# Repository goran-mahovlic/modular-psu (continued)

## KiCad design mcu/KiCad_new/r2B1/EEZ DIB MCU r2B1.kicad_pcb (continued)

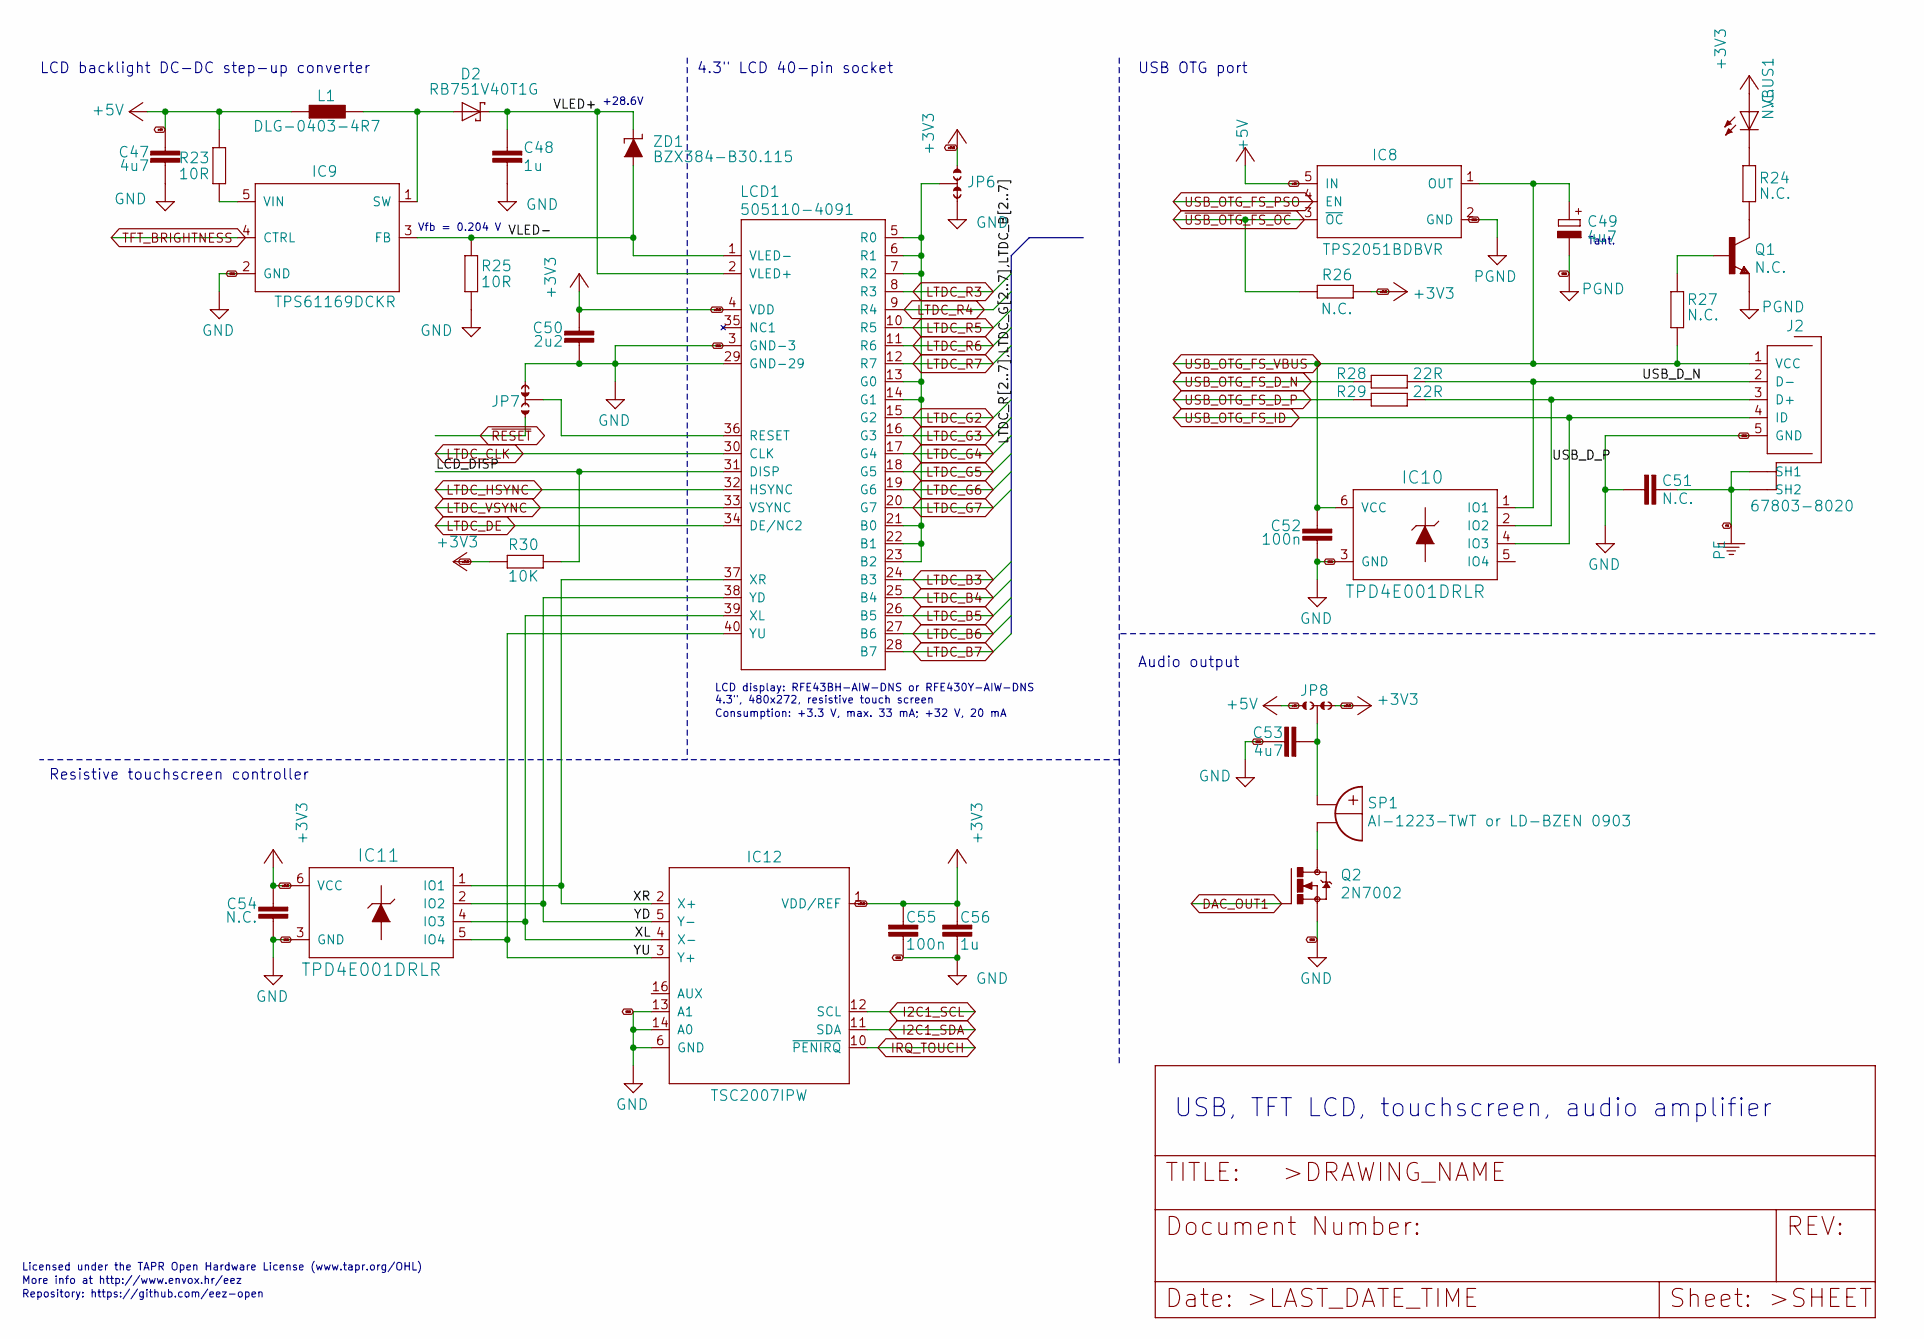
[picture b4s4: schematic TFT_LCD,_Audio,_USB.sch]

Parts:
C47, C53: 4u7; C1206
C48, C56: 1u; C0805
C49: 4u7; EC1206
C50: 2u2; C0805
C51: N.C.; C0805
C52, C55: 100n; C0603
C54: N.C.; C0603
D2: RB751V40T1G; SOD323-R
IC8: TPS2051BDBVR; DBV5
IC9: TPS61169DCKR; DCK5
IC10, IC11: TPD4E001DRLR; DRL6
IC12: TSC2007IPW; PW(R-PDSO-G16)
J2: 67803-8020; 678038020
JP6, JP7, JP8: JP3-CUT
L1: DLG-0403-4R7; DE0403
LCD1: 505110-4091; FPC_40
Q1: N.C.; SOT23-BEC
Q2: 2N7002; SOT103P240X110-3N
R23, R25: 10R; R0805
R24, R26, R27: N.C.; R0805
R28, R29: 22R; R0805
R30: 10K; R0805
SP1: AI-1223-TWT or LD-BZEN 0903; AI-1223-TWT_COMBO
VBUS: N.C.; LED_0805
ZD1: BZX384-B30.115; SOD323-W

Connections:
+3V3: C50.1, C54.2, C55.2, C56.2, IC11.6 (VCC), IC12.1 (VDD/REF), JP6.NO, JP8.NC, LCD1.4 (VDD), R26.2, R30.2; also elsewhere on the board
+5V: C47.1, IC8.5 (IN), JP8.NO, L1.1, R23.1; also elsewhere on the board
/TFT LCD, Audio, USB/LCD_DISP: LCD1.31 (DISP), R30.1
/TFT LCD, Audio, USB/USB_D_N: IC10.1 (IO1), J2.2 (D-), R28.1
/TFT LCD, Audio, USB/USB_D_P: IC10.2 (IO2), J2.3 (D+), R29.1
/TFT LCD, Audio, USB/VLED+: C48.1, D2.C, LCD1.2 (VLED+), ZD1.C
/TFT LCD, Audio, USB/VLED-: IC9.3 (FB), LCD1.1 (VLED-), R25.1, ZD1.A
/TFT LCD, Audio, USB/XL: IC11.4 (IO3), IC12.4 (X-), LCD1.39 (XL)
/TFT LCD, Audio, USB/XR: IC11.1 (IO1), IC12.2 (X+), LCD1.37 (XR)
/TFT LCD, Audio, USB/YD: IC11.2 (IO2), IC12.5 (Y-), LCD1.38 (YD)
/TFT LCD, Audio, USB/YU: IC11.5 (IO4), IC12.3 (Y+), LCD1.40 (YU)
DAC_OUT1: Q2.1 (G); also elsewhere on the board
GND: C47.2, C48.2, C49.-, C50.2, C51.2, C52.1, C53.1, C54.1, C55.1, C56.1, IC8.2 (GND), IC9.2 (GND), IC10.3 (GND), IC11.3 (GND), IC12.6 (GND), IC12.13 (A1), IC12.14 (A0), J2.5 (GND), JP6.NC, JP7.NC, LCD1.3 (GND-3), LCD1.29 (GND-29), Q1.E, Q2.2 (S), R25.2; also elsewhere on the board
I2C1_SCL: IC12.12 (SCL); also elsewhere on the board
I2C1_SDA: IC12.11 (SDA); also elsewhere on the board
IRQ_TOUCH: IC12.10 (~PENIRQ); also elsewhere on the board
LTDC_B3: LCD1.24 (B3); also elsewhere on the board
LTDC_B4: LCD1.25 (B4); also elsewhere on the board
LTDC_B5: LCD1.26 (B5); also elsewhere on the board
LTDC_B6: LCD1.27 (B6); also elsewhere on the board
LTDC_B7: LCD1.28 (B7); also elsewhere on the board
LTDC_CLK: LCD1.30 (CLK); also elsewhere on the board
LTDC_DE: LCD1.34 (DE/NC2); also elsewhere on the board
LTDC_G2: LCD1.15 (G2); also elsewhere on the board
LTDC_G3: LCD1.16 (G3); also elsewhere on the board
LTDC_G4: LCD1.17 (G4); also elsewhere on the board
LTDC_G5: LCD1.18 (G5); also elsewhere on the board
LTDC_G6: LCD1.19 (G6); also elsewhere on the board
LTDC_G7: LCD1.20 (G7); also elsewhere on the board
LTDC_HSYNC: LCD1.32 (HSYNC); also elsewhere on the board
LTDC_R3: LCD1.8 (R3); also elsewhere on the board
LTDC_R4: LCD1.9 (R4); also elsewhere on the board
LTDC_R5: LCD1.10 (R5); also elsewhere on the board
LTDC_R6: LCD1.11 (R6); also elsewhere on the board
LTDC_R7: LCD1.12 (R7); also elsewhere on the board
LTDC_VSYNC: LCD1.33 (VSYNC); also elsewhere on the board
unnamed: C53.2, JP8.COM, SP1.+B (+), SP1.+B.1 (+)
unnamed: D2.A, IC9.1 (SW), L1.2
unnamed: IC9.5 (VIN), R23.2
unnamed: JP6.COM, LCD1.5 (R0), LCD1.6 (R1), LCD1.7 (R2), LCD1.13 (G0), LCD1.14 (G1), LCD1.21 (B0), LCD1.22 (B1), LCD1.23 (B2)
unnamed: JP7.COM, LCD1.36 (RESET)
unnamed: Q1.B, R27.2
unnamed: Q1.C, R24.1
unnamed: Q2.3 (D), SP1.-B (-), SP1.-B.1 (-)
unnamed 195: R24.2; also elsewhere on the board
PE: C51.1, J2.SH1, J2.SH1.1 (SH1), J2.SH2, J2.SH2.2 (SH2); also elsewhere on the board
TFT_BRIGHTNESS: IC9.4 (CTRL); also elsewhere on the board
USB_OTG_FS_D_N: R28.2; also elsewhere on the board
USB_OTG_FS_D_P: R29.2; also elsewhere on the board
USB_OTG_FS_ID: IC10.4 (IO3), J2.4 (ID); also elsewhere on the board
USB_OTG_FS_PSO: IC8.4 (EN); also elsewhere on the board
USB_OTG_FS_VBUS: C49.+, C52.2, IC8.1 (OUT), IC10.6 (VCC), J2.1 (VCC), R27.1; also elsewhere on the board
~RESET: JP7.NO; also elsewhere on the board
~USB_OTG_FS_OC: IC8.3 (~OC), R26.1; also elsewhere on the board

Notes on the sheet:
USB, TFT LCD, touchscreen, audio amplifier
Licensed under the TAPR Open Hardware License (www.tapr.org/OHL)
Repository: https://github.com/eez-open
More info at http://www.envox.hr/eez
4.3" LCD 40-pin socket
LCD backlight DC-DC step-up converter
Consumption: +3.3 V, max. 33 mA; +32 V, 20 mA
Vfb = 0.204 V
LCD display: RFE43BH-AIW-DNS or RFE430Y-AIW-DNS 4.3", 480x272, resistive touch screen
USB OTG port
Resistive touchscreen controller
Audio output
Tant.
+28.6V

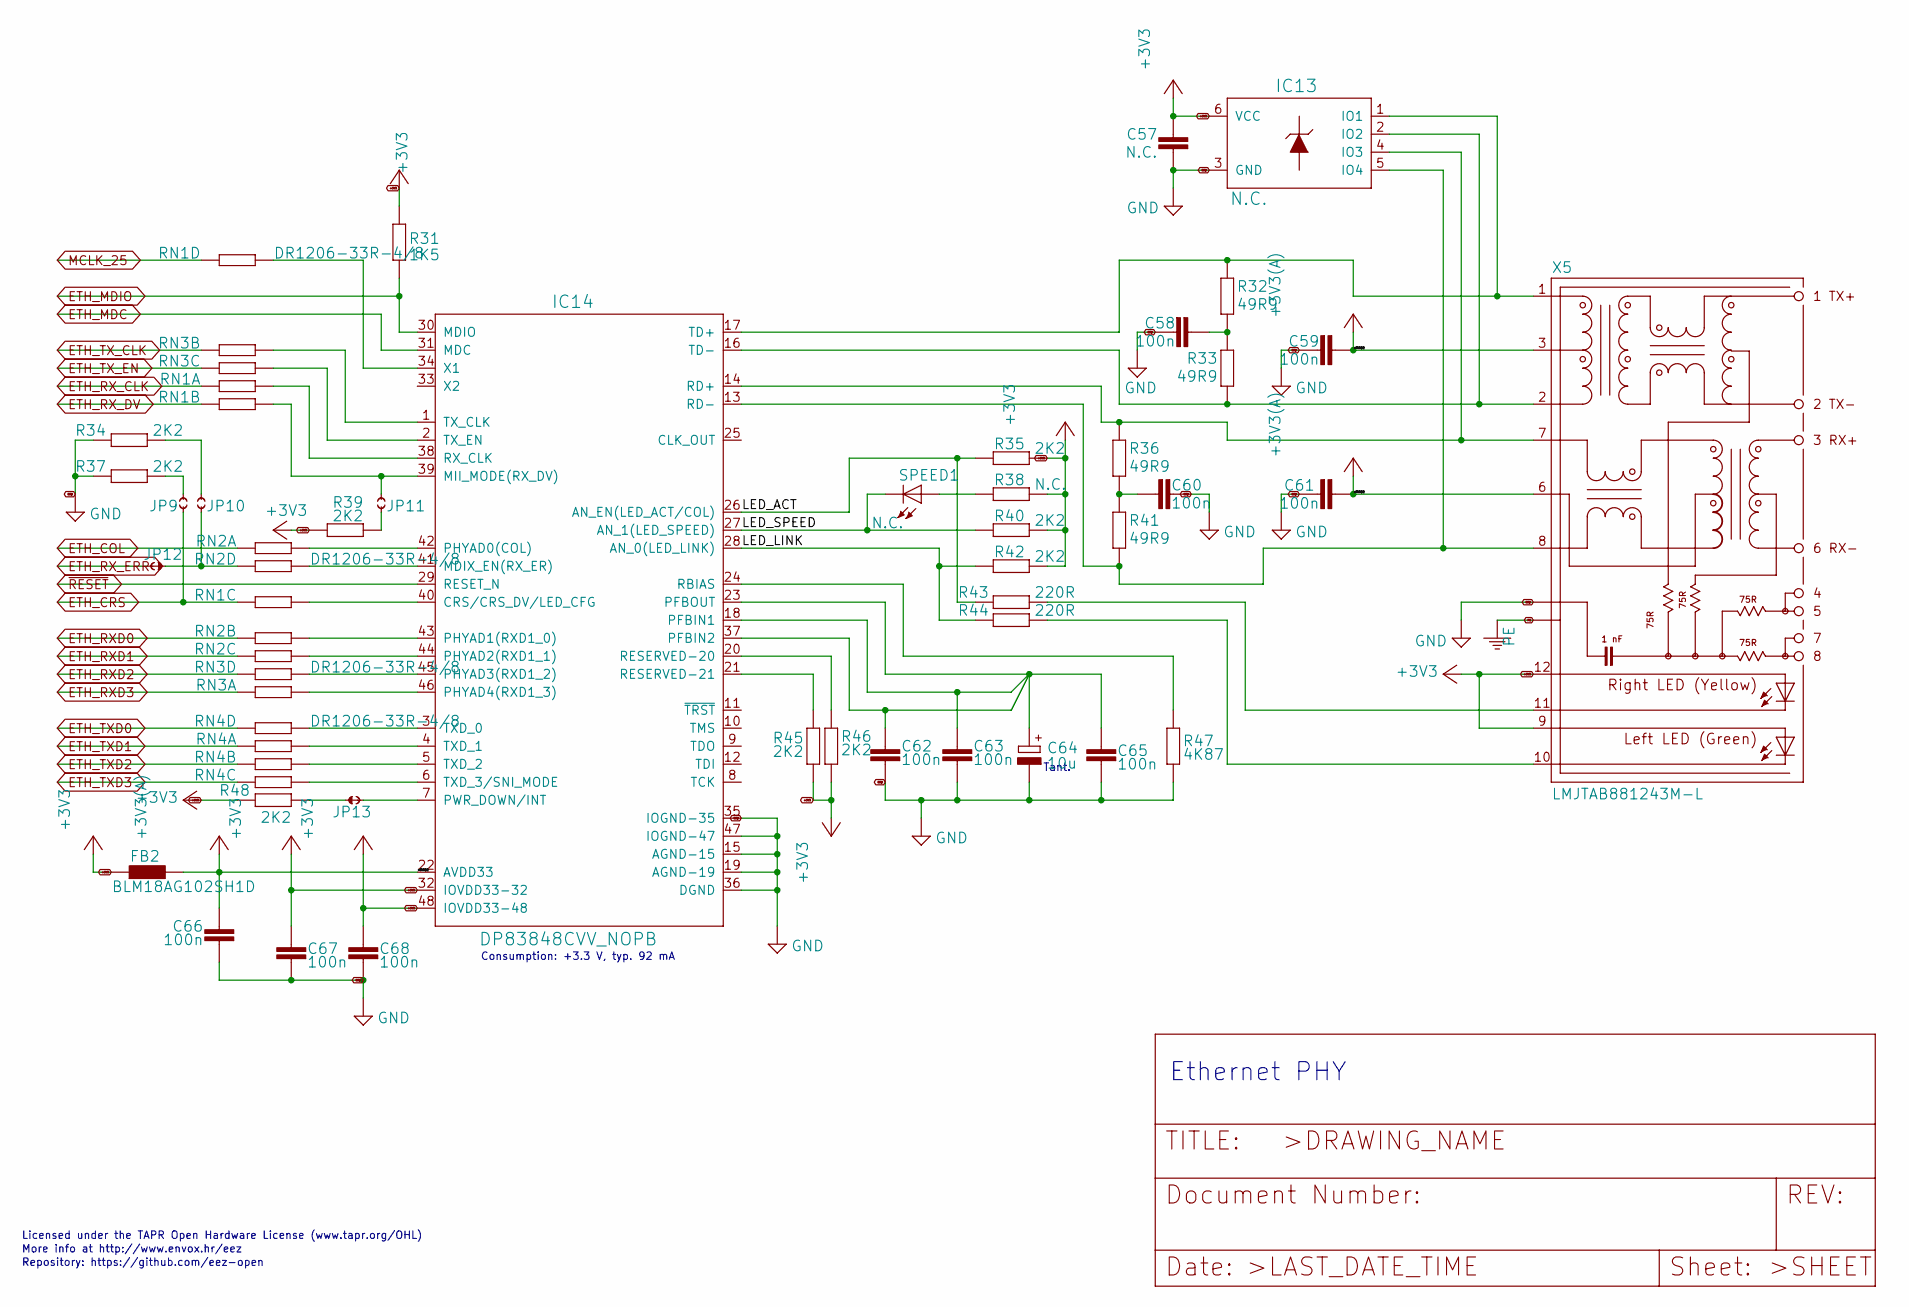
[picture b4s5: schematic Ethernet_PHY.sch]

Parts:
C57: N.C.; C0603
C58, C59, C60, C61, C62, C63, C65, C66, C67, C68: 100n; C0603
C64: 10u; EC1206
FB2: BLM18AG102SH1D; BEAD0603
IC13: N.C.; DRL6
IC14: DP83848CVV_NOPB; PT48
JP9, JP10, JP11: JP2-CUT
JP12, JP13: JP2-NOCUT
R31: 1K5; R0805
R32, R33, R36, R41: 49R9; R0805
R34, R35, R37, R39, R40, R42, R45, R46, R48: 2K2; R0805
R38: N.C.; R0805
R43, R44: 220R; R0805
R47: 4K87; R0805
RN1, RN2, RN3, RN4: DR1206-33R-4/8; CAY16
SPEED: N.C.; LED_0805
X5: LMJTAB881243M-L; RJ45-TRAFO-LED

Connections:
+3V3: C57.1, C67.1, C68.1, FB2.P$1 (1), IC13.6 (VCC), IC14.32 (IOVDD33-32), IC14.48 (IOVDD33-48), R31.2, R35.1, R38.1, R39.1, R40.1, R42.1, R45.1, R46.1, R48.1, X5.9 (GREEN-A), X5.12 (YELLOW_A); also elsewhere on the board
+3V3(A): C59.2, C61.2, C66.1, FB2.P$2 (2), IC14.22 (AVDD33), X5.3 (CT), X5.6 (CR)
/Ethernet PHY/LED_ACT: IC14.26 (AN_EN(LED_ACT/COL)), R35.2, R43.2
/Ethernet PHY/LED_LINK: IC14.28 (AN_0(LED_LINK)), R42.2, R44.2
/Ethernet PHY/LED_SPEED: IC14.27 (AN_1(LED_SPEED)), R40.2; also elsewhere on the board
ETH_COL: RN2.2 (1); also elsewhere on the board
ETH_CRS: JP9.1, RN1.4 (1); also elsewhere on the board
ETH_MDC: IC14.31 (MDC); also elsewhere on the board
ETH_MDIO: IC14.30 (MDIO), R31.1; also elsewhere on the board
ETH_RXD0: RN2.3 (1); also elsewhere on the board
ETH_RXD1: RN2.4 (1); also elsewhere on the board
ETH_RXD2: RN3.1; also elsewhere on the board
ETH_RXD3: RN3.2 (1); also elsewhere on the board
ETH_RX_CLK: RN1.2 (1); also elsewhere on the board
ETH_RX_DV: RN1.3 (1); also elsewhere on the board
ETH_RX_ERR: JP12.2; also elsewhere on the board
ETH_TXD0: RN4.1; also elsewhere on the board
ETH_TXD1: RN4.2 (1); also elsewhere on the board
ETH_TXD2: RN4.3 (1); also elsewhere on the board
ETH_TXD3: RN4.4 (1); also elsewhere on the board
ETH_TX_CLK: RN3.3 (1); also elsewhere on the board
ETH_TX_EN: RN3.4 (1); also elsewhere on the board
GND: C57.2, C58.2, C59.1, C60.2, C61.1, C62.2, C63.2, C64.-, C65.2, C66.2, C67.2, C68.2, IC13.3 (GND), IC14.15 (AGND-15), IC14.19 (AGND-19), IC14.35 (IOGND-35), IC14.36 (DGND), IC14.47 (IOGND-47), R34.1, R37.1, R47.1, X5.4 (GND), X5.5 (GND); also elsewhere on the board
MCLK_25: RN1.1; also elsewhere on the board
unnamed: C58.1, R32.1, R33.2
unnamed: C60.1, R36.1, R41.2
unnamed: C62.1, C63.1, C64.+, C65.1, IC14.18 (PFBIN1), IC14.23 (PFBOUT), IC14.37 (PFBIN2)
unnamed: IC13.1 (IO1), IC14.17 (TD+), R32.2, X5.1 (TD+)
unnamed: IC13.2 (IO2), IC14.16 (TD-), R33.1, X5.2 (TD-)
unnamed: IC13.4 (IO3), IC14.14 (RD+), R36.2, X5.7 (RD+)
unnamed: IC13.5 (IO4), IC14.13 (RD-), R41.1, X5.8 (RD-)
unnamed: IC14.1 (TX_CLK), RN3.6 (2)
unnamed: IC14.2 (TX_EN), RN3.5 (2)
unnamed: IC14.3 (TXD_0), RN4.8 (2)
unnamed: IC14.4 (TXD_1), RN4.7 (2)
unnamed: IC14.5 (TXD_2), RN4.6 (2)
unnamed: IC14.6 (TXD_3/SNI_MODE), RN4.5 (2)
unnamed: IC14.7 (PWR_DOWN/INT), JP13.2
unnamed: IC14.20 (RESERVED-20), R46.2
unnamed: IC14.21 (RESERVED-21), R45.2
unnamed: IC14.24 (RBIAS), R47.2
unnamed: IC14.34 (X1), RN1.8 (2)
unnamed: IC14.38 (RX_CLK), RN1.7 (2)
unnamed: IC14.39 (MII_MODE(RX_DV)), JP11.2, RN1.6 (2)
unnamed: IC14.40 (CRS/CRS_DV/LED_CFG), RN1.5 (2)
unnamed: IC14.41 (MDIX_EN(RX_ER)), RN2.8 (2)
unnamed: IC14.42 (PHYAD0(COL)), RN2.7 (2)
unnamed: IC14.43 (PHYAD1(RXD1_0)), RN2.6 (2)
unnamed: IC14.44 (PHYAD2(RXD1_1)), RN2.5 (2)
unnamed: IC14.45 (PHYAD3(RXD1_2)), RN3.8 (2)
unnamed: IC14.46 (PHYAD4(RXD1_3)), RN3.7 (2)
unnamed: JP9.2, R37.2
unnamed: JP10.1, JP12.1, RN2.1
unnamed: JP10.2, R34.2
unnamed: JP11.1, R39.2
unnamed: JP13.1, R48.2
unnamed 196: R38.2; also elsewhere on the board
unnamed: R43.1, X5.11 (YELLOW-C)
unnamed: R44.1, X5.10 (GREEN-C)
PE: X5.SH, X5.SH2 (SH); also elsewhere on the board
~RESET: IC14.29 (RESET_N); also elsewhere on the board

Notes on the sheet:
Ethernet PHY
Tant.
Consumption: +3.3 V, typ. 92 mA
Licensed under the TAPR Open Hardware License (www.tapr.org/OHL)
Repository: https://github.com/eez-open
More info at http://www.envox.hr/eez

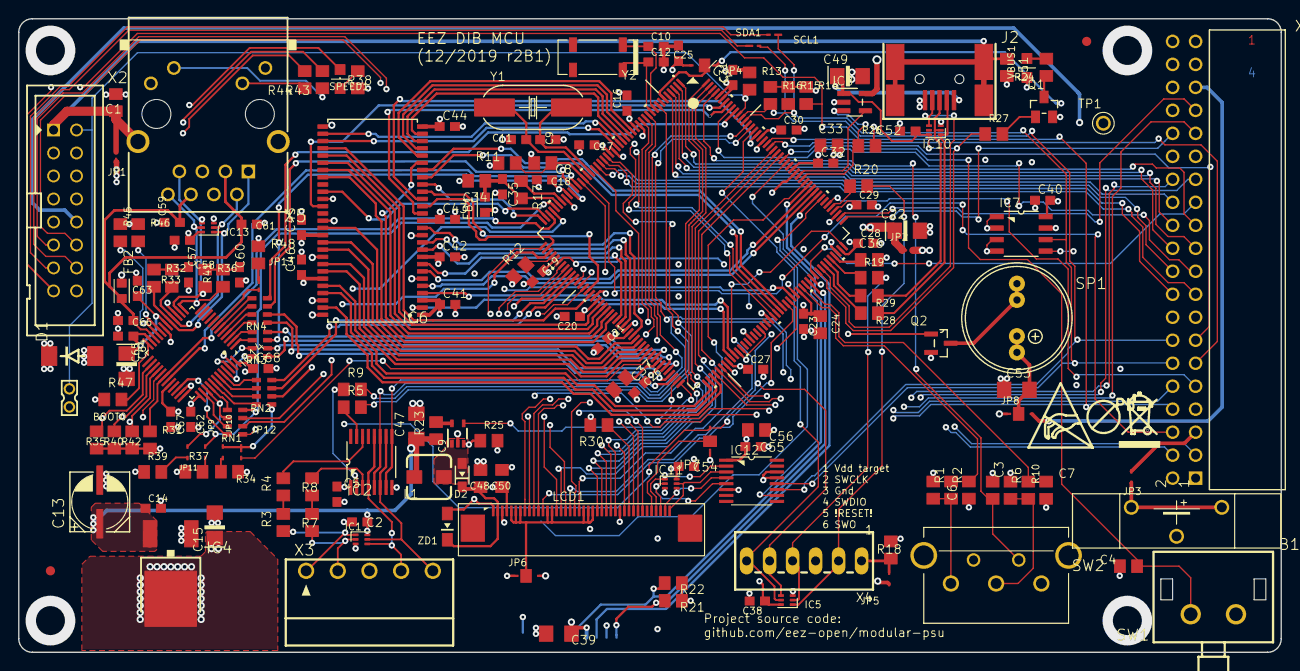
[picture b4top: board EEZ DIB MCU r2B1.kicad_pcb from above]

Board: 4 copper layers, 139.5 x 70.0 mm, 181 parts (0 on the bottom side), 219 nets.

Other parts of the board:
EEZ_SIGNATURE: SIGNATURESMALL; SIGNATURE_5MM
SCL1: JP2-NOCUT
SDA1: JP2-NOCUT
SPEED1: N.C.; LED_0805
U$1: RECYCLE_BIN1_8
U$5: PB_SMALL
U$6: ESD_SYMBOL
VBUS1: N.C.; LED_0805

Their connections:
+3V3: VBUS1.A; also elsewhere on the board
/Ethernet PHY/LED_SPEED: SPEED1.C; also elsewhere on the board
I2C1_SCL: SCL1.1; also elsewhere on the board
I2C1_SDA: SDA1.2; also elsewhere on the board
unnamed 195: VBUS1.C; also elsewhere on the board
unnamed 196: SPEED1.A; also elsewhere on the board
unnamed 199: SCL1.2; also elsewhere on the board
unnamed 200: SDA1.1; also elsewhere on the board

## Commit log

2020-01-06 Converting all designs to KiCad
2020-01-07 Adding initial 3D images for BP3C
2020-01-07 Fixing Blender export - hand needs to be removed from PCB for export
2020-01-07 Adding freecad connected - adding pins to modules
